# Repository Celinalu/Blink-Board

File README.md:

# Blink Board
A flashing carrot blink board!!!
This carrot will not help your eyesight but will help you see in the dark with it's led lights. This is a pocket-sized, carrot-shaped PBC that uses an oscillator circuit to make LEDs flash. Since I only used transistors and capacitors, there is no code needed for this project.

## How to use it
To use it all you need to do is to connect the blink board to a battery, and then flip the switch to start. If the lights are flicking then that means it's working!

## Why I made it
I was motivated  to create this since it was fairly stirghtforward in the sense that there isn't any coding that have to be done. I also wanted to create this because I thought it would look like a really cool keychain.

# Fallout Zine

# Gallery
 schematic editor

PCD design of carrot blink board

3D model of the PCB

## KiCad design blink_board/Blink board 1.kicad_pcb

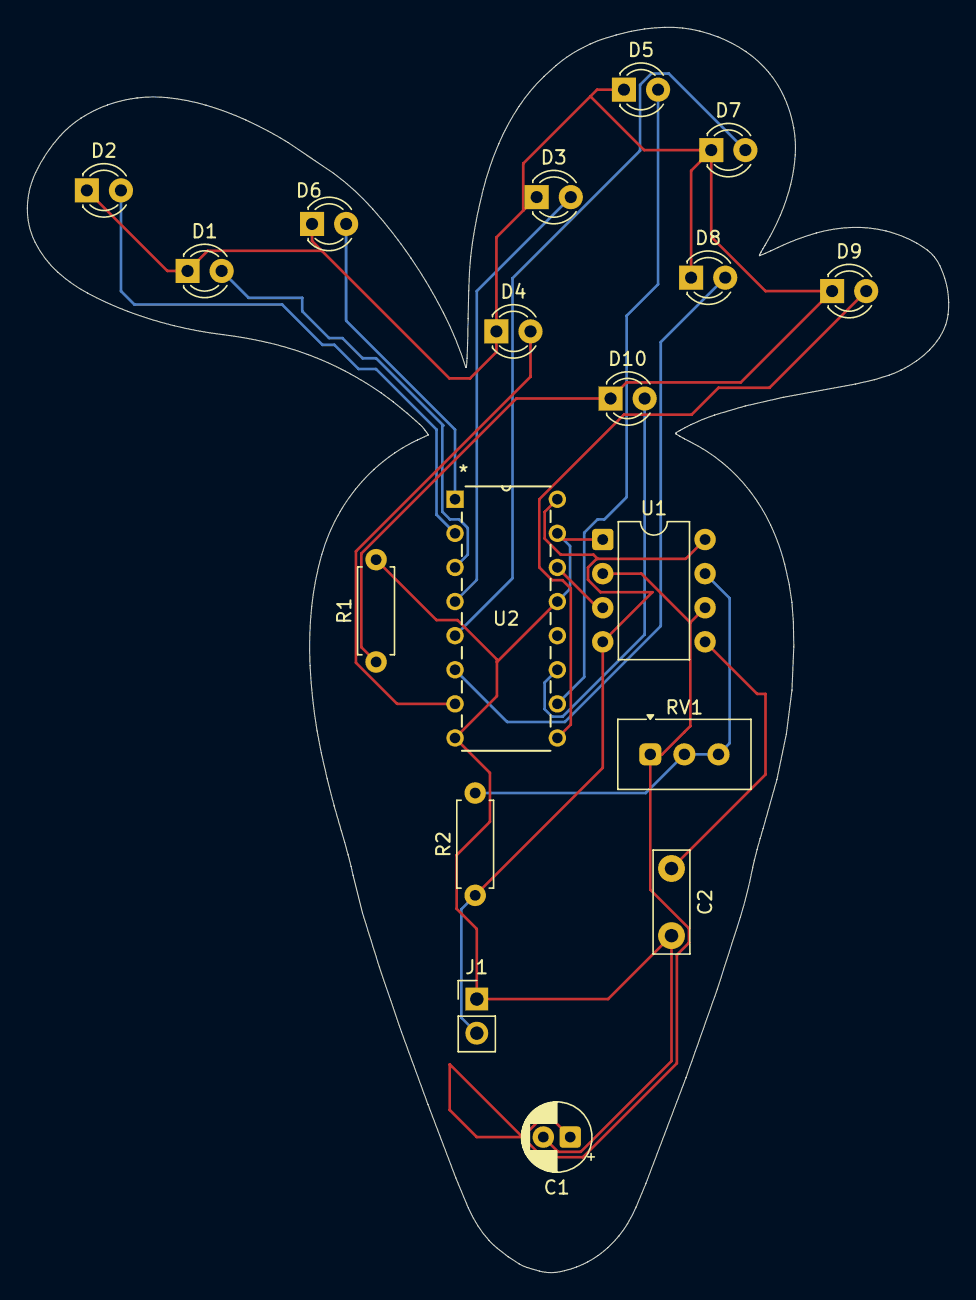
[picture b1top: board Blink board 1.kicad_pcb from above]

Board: 2 copper layers, 68.6 x 92.7 mm, 18 parts (0 on the bottom side), 17 nets.

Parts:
C1: C_Polarized; CP_Radial_D5.0mm_P2.00mm
C2: C; C_Disc_D7.5mm_W2.5mm_P5.00mm
D1, D2, D3, D4, D5, D6, D7, D8, D9, D10: LED; LED_D3.0mm
J1: Conn_01x02_Socket; PinHeader_1x02_P2.54mm_Vertical
R1, R2: R; R_Axial_DIN0207_L6.3mm_D2.5mm_P7.62mm_Horizontal
RV1: R_Potentiometer; Potentiometer_Vishay_T93YA_Vertical
U1: NE555P; DIP-8_W7.62mm
U2: 4017; N16

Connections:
+5V: J1.2, R2.1, U1.4 (~RST), U1.8 (VCC), U2.16 (VDD)
/OUT: U1.3 (OUT), U2.14 (CLK)
/TR: C1.1, RV1.1, U1.2 (TRIG), U1.6 (THRES)
GND: C1.2, C2.2, J1.1, R1.2, U1.1 (GND), U2.8 (VSS), U2.13 (CKEN), U2.15 (Reset)
unnamed: D1.2 (A), U2.3 (Q0)
unnamed: D1.1 (K), D2.1 (K), D3.1 (K), D4.1 (K), D5.1 (K), D6.1 (K), D7.1 (K), D8.1 (K), D9.1 (K), D10.1 (K), R1.1
unnamed: D2.2 (A), U2.2 (Q1)
unnamed: D3.2 (A), U2.4 (Q2)
unnamed: D4.2 (A), U2.7 (Q3)
unnamed: D5.2 (A), U2.10 (Q4)
unnamed: D6.2 (A), U2.1 (Q5)
unnamed: D7.2 (A), U2.5 (Q6)
unnamed: D8.2 (A), U2.6 (Q7)
unnamed: D9.2 (A), U2.9 (Q8)
unnamed: D10.2 (A), U2.11 (Q9)
unnamed: C2.1, U1.5 (CONT)
unnamed: R2.2, RV1.2, RV1.3, U1.7 (DISCH)

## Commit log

2026-04-03 did my schematic part
    Crashed the first did redid everything a second time :(((
2026-04-03 forgot part of my schematic
    forgot a part of it
2026-04-03 Finished my schematic and tracing
    struggled but finished the tracing now need to send picture of parts to fallout
2026-04-04 Update README.md
    writing the readme still got to do the poster
2026-04-04 Update README.md
    adding the poster into the readme
2026-04-04 Update README.md
    forgot the bom was not suppose to go here, didnt change naything
2026-04-04 Delete Untitled spreadsheet - Sheet1.csv
    need to rename it
2026-04-04 Update README.md
    added why i made this part
2026-04-04 Update README.md
    added sub labels
2026-04-19 Delete Blink board 1 directory
    fixing repo to look better
2026-04-19 Delete Blink board1gerbers.zip
    fixing repo
2026-04-19 Delete Carrot Blink Board.pdf
    redoing repo
2026-04-20 Delete Blink_Board PCB directory
    want to change the name of the file
2026-04-20 just editing for polishing
2026-04-20 adding everything in
2026-04-27 Delete blink_board_gerbers/Blink board1gerbers.zip
    replacing this
2026-04-27 changed the zine page
    Added a link to the Carrot Blink Board PDF in the README.
2026-04-27 Add image and correct typos in README
    Updated README to include an image and fix typos.
